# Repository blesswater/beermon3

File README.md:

beermon3

This is the thrid resurection of my beer refrigerator controller.

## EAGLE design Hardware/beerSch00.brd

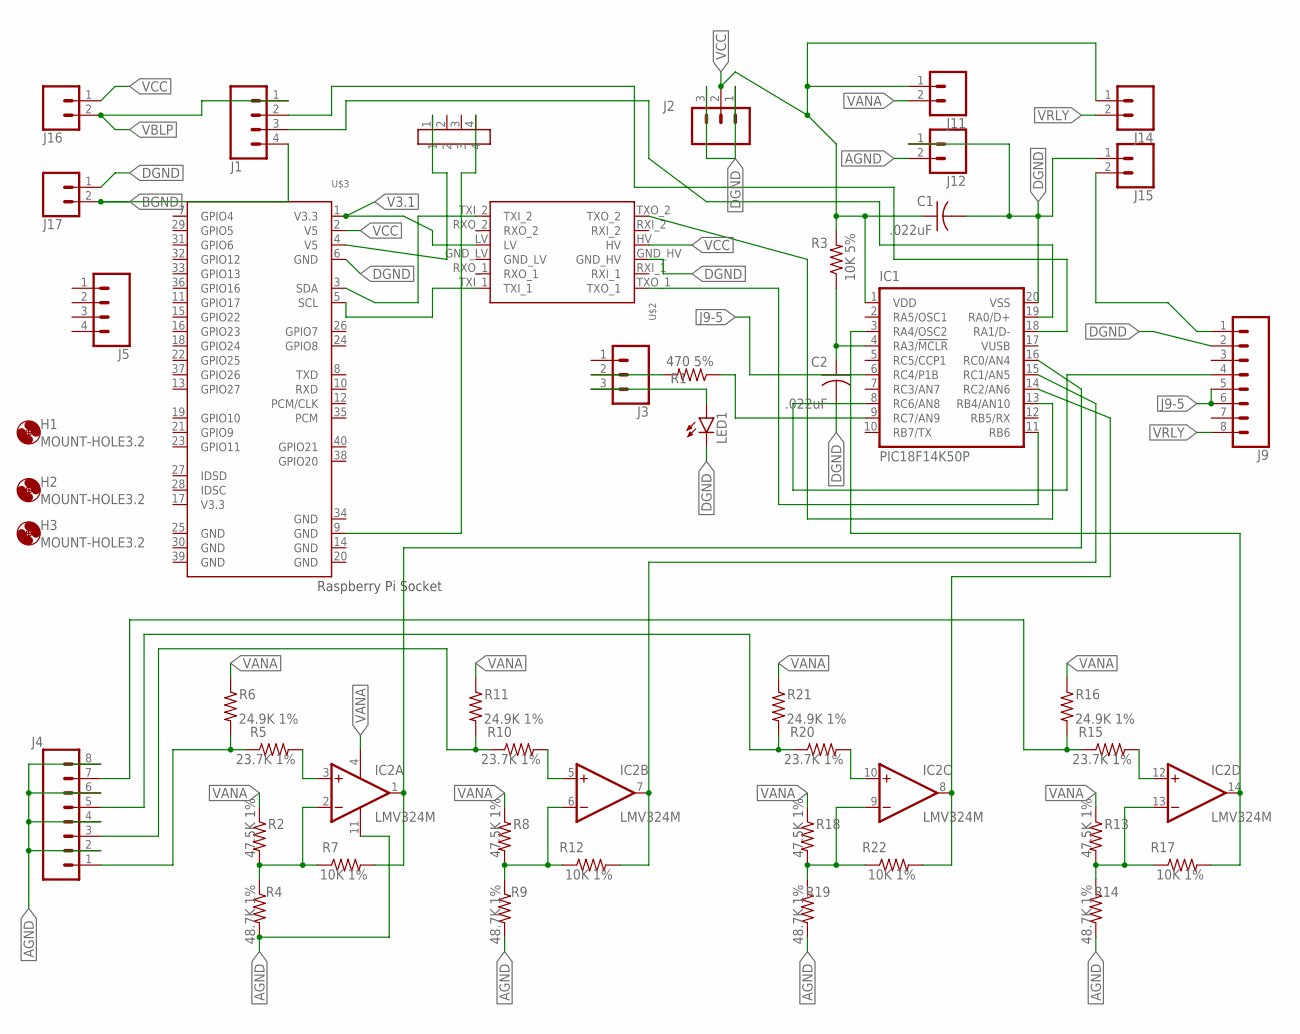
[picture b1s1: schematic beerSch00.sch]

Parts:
C1, C2: .022uF; C0805
H1, H2, H3: MOUNT-HOLE3.2; 3,2
IC1: PIC18F14K50P; DIL20
IC2: LMV324M; SO14
J1, J5: CONN_04; 1X04
J2, J3: CONN_03; 1X03
J4, J9: CONN_08"; 1X08
J11, J12, J14, J15, J16, J17: CONN_02; 1X02
LED1: LEDSML0805; SML0805
R1: 470 5%; R0603
R2, R8, R13, R18: 47.5K 1%; R0603
R3: 10K 5%; R0603
R4, R9, R14, R19: 48.7K 1%; R0603
R5, R10, R15, R20: 23.7K 1%; R0603
R6, R11, R16, R21: 24.9K 1%; R0603
R7, R12, R17, R22: 10K 1%; R0603
U$1: CONN_4; PINS_90
U$2: LEVELCONV; PLUG_THROUGHHOLE
U$3: RASPBERRYPI_SOCKET_UNDER; RASPBERRYPI_UNDERBD

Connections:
AGND: IC2.11 (V-), J4.2, J4.4, J4.6, J4.8, J12.2, R4.2, R9.2, R14.2, R19.2
BGND: J1.4, J17.2
DGND: C1.2, C2.2, IC1.20 (VSS), J2.1, J2.3, J9.2, J12.1, J15.1, J17.1, LED1.C, U$2.GND_HV, U$3.6 (GND)
J9-5: IC1.6 (RC4/P1B), J9.5, J9.6
unnamed: U$2.TXI_2, U$3.3 (SDA)
unnamed: U$2.TXI_1, U$3.5 (SCL)
unnamed: IC1.13 (RB4/AN10), U$2.TXO_2
unnamed: IC1.11 (RB6), U$2.TXO_1
unnamed: C2.1, IC1.4 (RA3/!MCLR!), R3.1
unnamed: J3.2, R1.2
unnamed: IC1.9 (RC7/AN9), R1.1
unnamed: J3.3, LED1.A
unnamed: IC2.2 (-IN), R2.2, R4.1, R7.1
unnamed: J4.1, R5.1, R6.2
unnamed: IC2.3 (+IN), R5.2
unnamed: IC1.16 (RC0/AN4), IC2.1 (OUT), R7.2
unnamed: IC2.6 (-IN), R8.2, R9.1, R12.1
unnamed: J4.3, R10.1, R11.2
unnamed: IC2.5 (+IN), R10.2
unnamed: J9.1, J15.2
unnamed: U$1.4, U$3.9 (GND)
unnamed: IC2.13 (-IN), R13.2, R14.1, R17.1
unnamed: J4.7, R15.1, R16.2
unnamed: IC2.12 (+IN), R15.2
unnamed: IC1.8 (RC6/AN8), J9.4
unnamed: IC2.9 (-IN), R18.2, R19.1, R22.1
unnamed: J4.5, R20.1, R21.2
unnamed: IC2.10 (+IN), R20.2
unnamed: U$1.1, U$3.4 (V5)
unnamed: IC1.19 (RA0/D+), J1.3
unnamed: IC1.3 (RA4/OSC2), IC2.14 (OUT), R17.2
unnamed: IC1.14 (RC2/AN6), IC2.8 (OUT), R22.2
unnamed: IC1.15 (RC1/AN5), IC2.7 (OUT), R12.2
unnamed: IC1.18 (RA1/D-), J1.2
V3.1: U$2.LV, U$3.1 (V3.3)
VANA: IC2.4 (V+), J11.2, R2.1, R6.1, R8.1, R11.1, R13.1, R16.1, R18.1, R21.1
VBLP: J1.1, J16.2
VCC: C1.1, IC1.1 (VDD), J2.2, J11.1, J14.1, J16.1, R3.2, U$2.HV, U$3.2 (V5)
VRLY: J9.8, J14.2

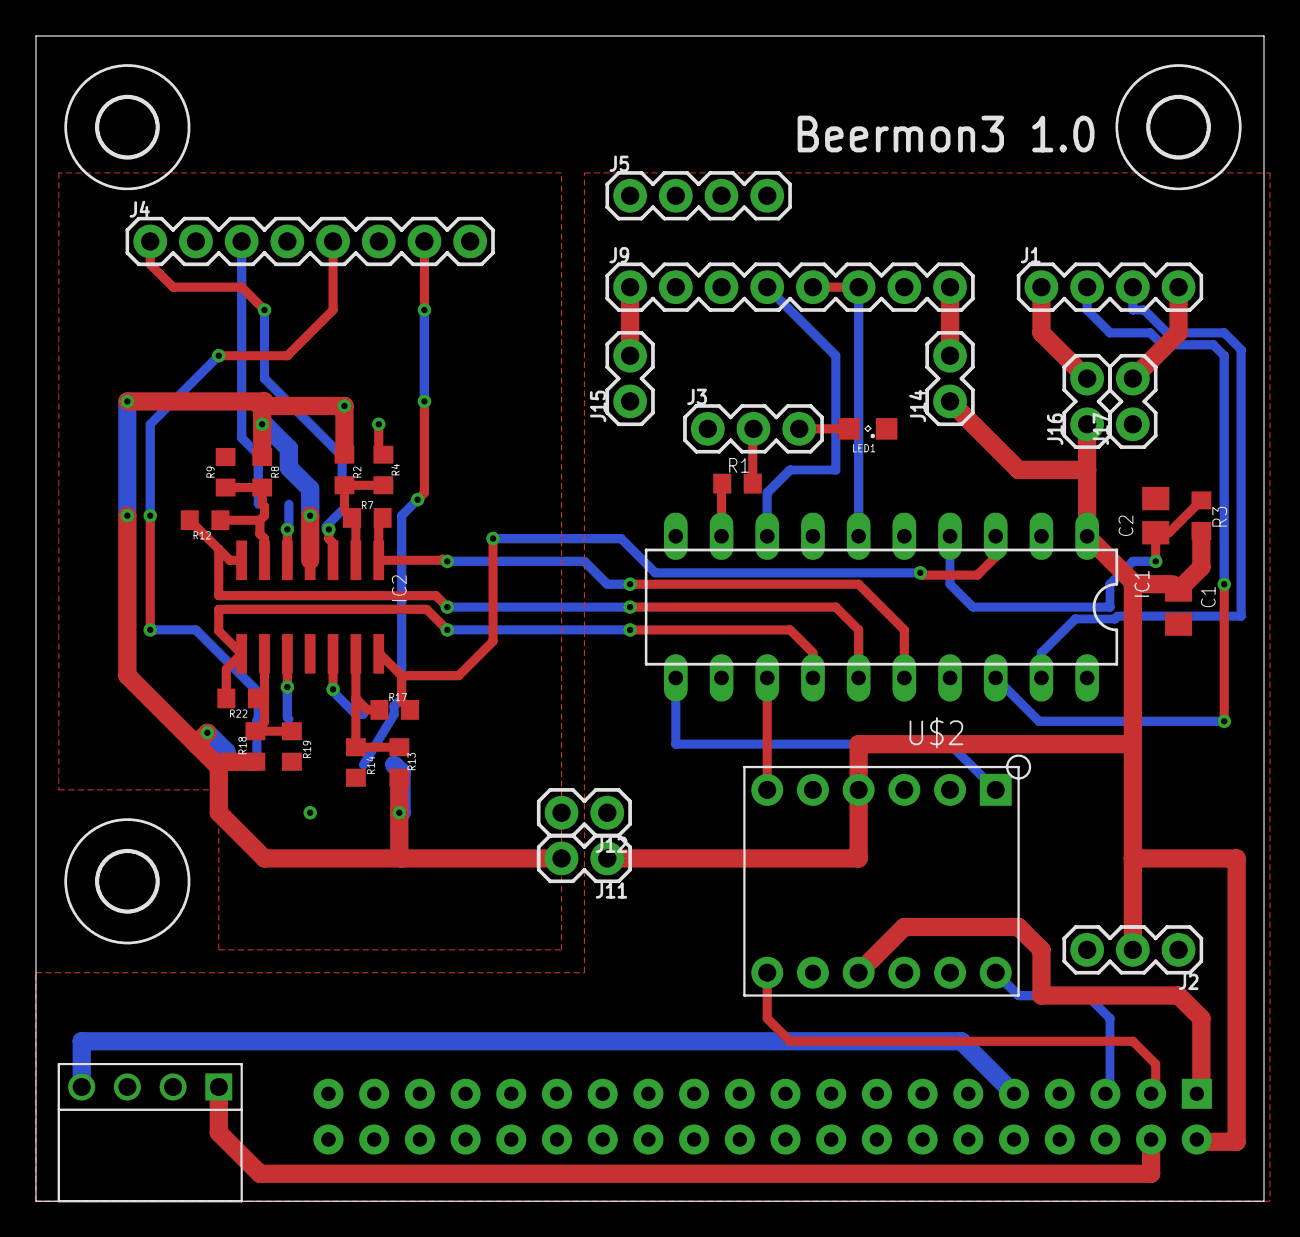
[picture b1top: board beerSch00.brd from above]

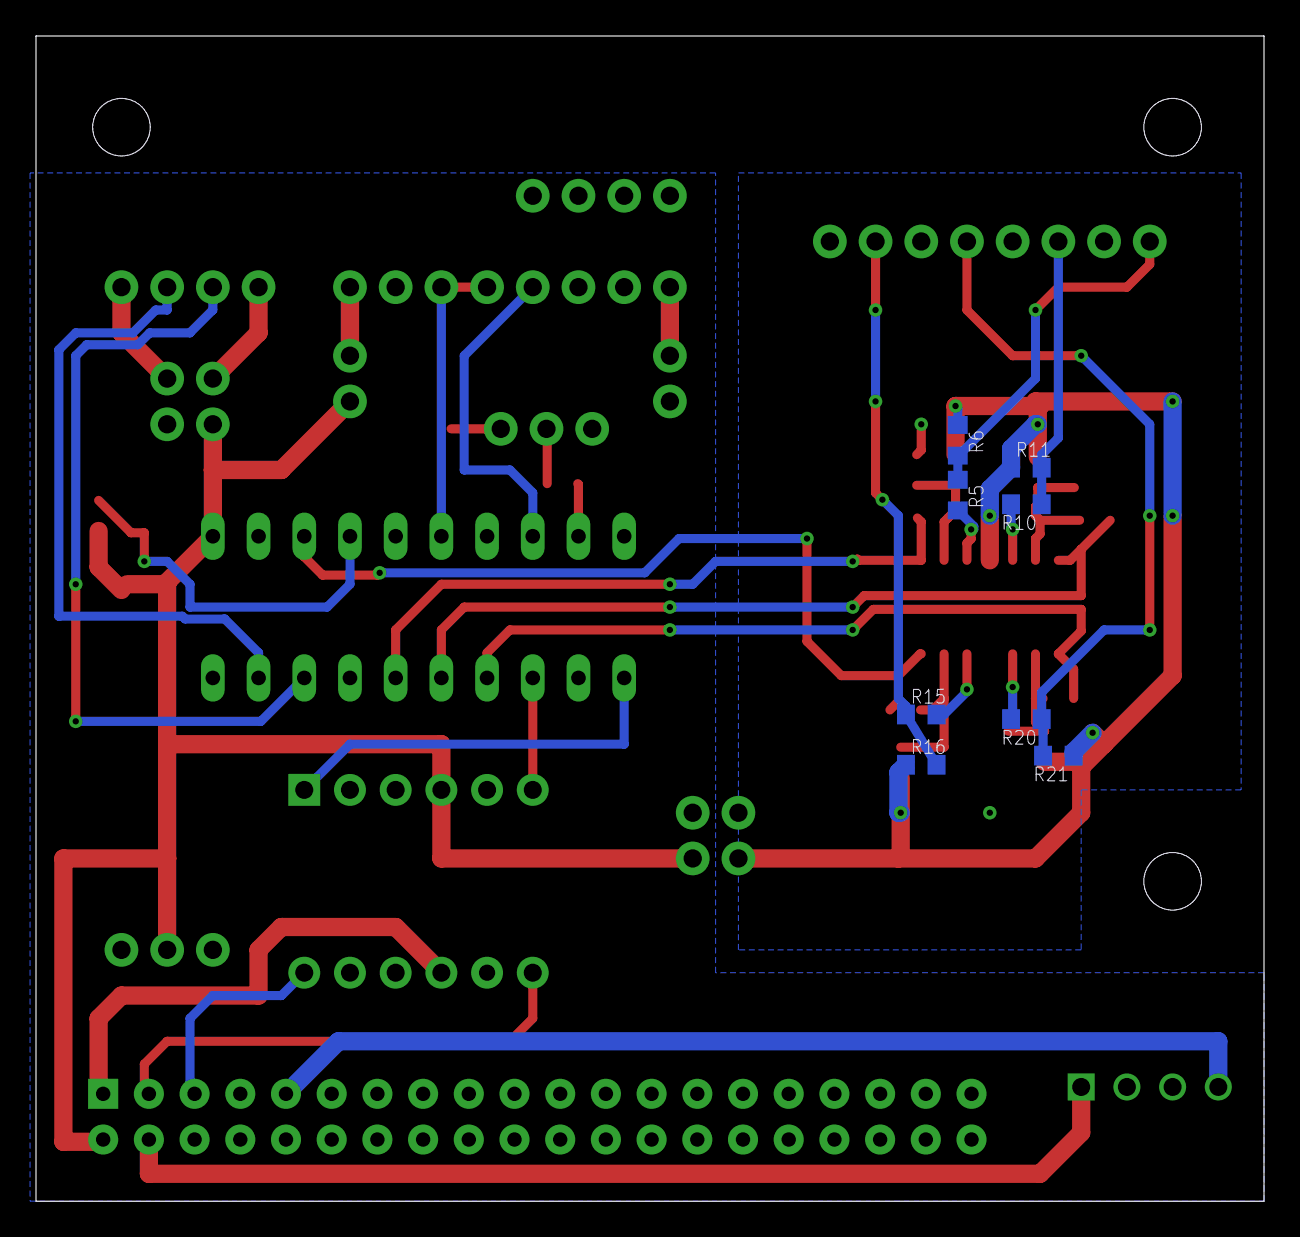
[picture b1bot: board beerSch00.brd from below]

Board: 2 copper layers, 68.2 x 64.8 mm, 45 parts (8 on the bottom side), 39 nets.

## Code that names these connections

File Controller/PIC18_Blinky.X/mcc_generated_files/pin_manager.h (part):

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// get/set channel_AN3 aliases
#define channel_AN3_TRIS                 TRISAbits.TRISA4
#define channel_AN3_LAT                  LATAbits.LATA4
#define channel_AN3_PORT                 PORTAbits.RA4
#define channel_AN3_WPU                  WPUAbits.WPUA4
#define channel_AN3_ANS                  ANSELbits.ANS3
#define channel_AN3_SetHigh()            do { LATAbits.LATA4 = 1; } while(0)
#define channel_AN3_SetLow()             do { LATAbits.LATA4 = 0; } while(0)
#define channel_AN3_Toggle()             do { LATAbits.LATA4 = ~LATAbits.LATA4; } while(0)
#define channel_AN3_GetValue()           PORTAbits.RA4
#define channel_AN3_SetDigitalInput()    do { TRISAbits.TRISA4 = 1; } while(0)
#define channel_AN3_SetDigitalOutput()   do { TRISAbits.TRISA4 = 0; } while(0)
#define channel_AN3_SetPullup()          do { WPUAbits.WPUA4 = 1; } while(0)
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// get/set SDA1 aliases
#define SDA1_TRIS                 TRISBbits.TRISB4
#define SDA1_LAT                  LATBbits.LATB4
#define SDA1_PORT                 PORTBbits.RB4
#define SDA1_WPU                  WPUBbits.WPUB4
#define SDA1_ANS                  ANSELHbits.ANS10
#define SDA1_SetHigh()            do { LATBbits.LATB4 = 1; } while(0)
#define SDA1_SetLow()             do { LATBbits.LATB4 = 0; } while(0)
#define SDA1_Toggle()             do { LATBbits.LATB4 = ~LATBbits.LATB4; } while(0)
#define SDA1_GetValue()           PORTBbits.RB4
#define SDA1_SetDigitalInput()    do { TRISBbits.TRISB4 = 1; } while(0)
#define SDA1_SetDigitalOutput()   do { TRISBbits.TRISB4 = 0; } while(0)
#define SDA1_SetPullup()          do { WPUBbits.WPUB4 = 1; } while(0)
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// get/set SCL1 aliases
#define SCL1_TRIS                 TRISBbits.TRISB6
#define SCL1_LAT                  LATBbits.LATB6
#define SCL1_PORT                 PORTBbits.RB6
#define SCL1_WPU                  WPUBbits.WPUB6
#define SCL1_SetHigh()            do { LATBbits.LATB6 = 1; } while(0)
#define SCL1_SetLow()             do { LATBbits.LATB6 = 0; } while(0)
#define SCL1_Toggle()             do { LATBbits.LATB6 = ~LATBbits.LATB6; } while(0)
#define SCL1_GetValue()           PORTBbits.RB6
#define SCL1_SetDigitalInput()    do { TRISBbits.TRISB6 = 1; } while(0)
#define SCL1_SetDigitalOutput()   do { TRISBbits.TRISB6 = 0; } while(0)
#define SCL1_SetPullup()          do { WPUBbits.WPUB6 = 1; } while(0)
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// get/set channel_AN4 aliases
#define channel_AN4_TRIS                 TRISCbits.TRISC0
#define channel_AN4_LAT                  LATCbits.LATC0
#define channel_AN4_PORT                 PORTCbits.RC0
#define channel_AN4_ANS                  ANSELbits.ANS4
#define channel_AN4_SetHigh()            do { LATCbits.LATC0 = 1; } while(0)
#define channel_AN4_SetLow()             do { LATCbits.LATC0 = 0; } while(0)
#define channel_AN4_Toggle()             do { LATCbits.LATC0 = ~LATCbits.LATC0; } while(0)
#define channel_AN4_GetValue()           PORTCbits.RC0
#define channel_AN4_SetDigitalInput()    do { TRISCbits.TRISC0 = 1; } while(0)
#define channel_AN4_SetDigitalOutput()   do { TRISCbits.TRISC0 = 0; } while(0)
#define channel_AN4_SetAnalogMode()      do { ANSELbits.ANS4 = 1; } while(0)
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// get/set channel_AN5 aliases
#define channel_AN5_TRIS                 TRISCbits.TRISC1
#define channel_AN5_LAT                  LATCbits.LATC1
#define channel_AN5_PORT                 PORTCbits.RC1
#define channel_AN5_ANS                  ANSELbits.ANS5
#define channel_AN5_SetHigh()            do { LATCbits.LATC1 = 1; } while(0)
#define channel_AN5_SetLow()             do { LATCbits.LATC1 = 0; } while(0)
#define channel_AN5_Toggle()             do { LATCbits.LATC1 = ~LATCbits.LATC1; } while(0)
#define channel_AN5_GetValue()           PORTCbits.RC1
#define channel_AN5_SetDigitalInput()    do { TRISCbits.TRISC1 = 1; } while(0)
#define channel_AN5_SetDigitalOutput()   do { TRISCbits.TRISC1 = 0; } while(0)
#define channel_AN5_SetAnalogMode()      do { ANSELbits.ANS5 = 1; } while(0)
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// get/set channel_AN6 aliases
#define channel_AN6_TRIS                 TRISCbits.TRISC2
#define channel_AN6_LAT                  LATCbits.LATC2
#define channel_AN6_PORT                 PORTCbits.RC2
#define channel_AN6_ANS                  ANSELbits.ANS6
#define channel_AN6_SetHigh()            do { LATCbits.LATC2 = 1; } while(0)
#define channel_AN6_SetLow()             do { LATCbits.LATC2 = 0; } while(0)
#define channel_AN6_Toggle()             do { LATCbits.LATC2 = ~LATCbits.LATC2; } while(0)
#define channel_AN6_GetValue()           PORTCbits.RC2
#define channel_AN6_SetDigitalInput()    do { TRISCbits.TRISC2 = 1; } while(0)
#define channel_AN6_SetDigitalOutput()   do { TRISCbits.TRISC2 = 0; } while(0)
#define channel_AN6_SetAnalogMode()      do { ANSELbits.ANS6 = 1; } while(0)
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// get/set IO_RC6 aliases
#define IO_RC6_TRIS                 TRISCbits.TRISC6
#define IO_RC6_LAT                  LATCbits.LATC6
#define IO_RC6_PORT                 PORTCbits.RC6
#define IO_RC6_ANS                  ANSELHbits.ANS8
#define IO_RC6_SetHigh()            do { LATCbits.LATC6 = 1; } while(0)
#define IO_RC6_SetLow()             do { LATCbits.LATC6 = 0; } while(0)
#define IO_RC6_Toggle()             do { LATCbits.LATC6 = ~LATCbits.LATC6; } while(0)
#define IO_RC6_GetValue()           PORTCbits.RC6
#define IO_RC6_SetDigitalInput()    do { TRISCbits.TRISC6 = 1; } while(0)
#define IO_RC6_SetDigitalOutput()   do { TRISCbits.TRISC6 = 0; } while(0)
#define IO_RC6_SetAnalogMode()      do { ANSELHbits.ANS8 = 1; } while(0)
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// get/set IO_RC7 aliases
#define IO_RC7_TRIS                 TRISCbits.TRISC7
#define IO_RC7_LAT                  LATCbits.LATC7
#define IO_RC7_PORT                 PORTCbits.RC7
#define IO_RC7_ANS                  ANSELHbits.ANS9
#define IO_RC7_SetHigh()            do { LATCbits.LATC7 = 1; } while(0)
#define IO_RC7_SetLow()             do { LATCbits.LATC7 = 0; } while(0)
#define IO_RC7_Toggle()             do { LATCbits.LATC7 = ~LATCbits.LATC7; } while(0)
#define IO_RC7_GetValue()           PORTCbits.RC7
#define IO_RC7_SetDigitalInput()    do { TRISCbits.TRISC7 = 1; } while(0)
#define IO_RC7_SetDigitalOutput()   do { TRISCbits.TRISC7 = 0; } while(0)
#define IO_RC7_SetAnalogMode()      do { ANSELHbits.ANS9 = 1; } while(0)
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
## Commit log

2018-03-24 Simple Blinky Running
2018-10-24 Add beerChip Project
2018-10-24 Remove lost files
2018-10-24 Change main
2018-10-24 Fixed arbituary file locations
2018-10-27 Added beerChip.ISR.c
2018-10-27 Got timer1 working
2018-10-30 Got I2C working
2018-10-30 Got LED control
2018-11-01 Got locks working
2018-11-02 Got MPLab v5.05 working
2018-11-02 Tested PIC3 on v5.05
2018-11-02 Commit stuff I do not want to commit to get merge to work
2018-11-02 Post-merge
2018-11-07 Add A2D files
2018-11-07 Worked on I2C A/D I/F
2018-11-07 Make build
2018-11-08 Got Chan 1 A/D working
2018-11-08 Version b
2018-11-09 Add thermister table
2018-11-11 Moved LED to RC7
2018-11-11 Added calculations
2018-11-21 Build beerChipTempLookup.c
2018-11-21 Before temp reading trigger
2018-11-21 Fixed bug in temp lookup
2018-11-22 Add user timer
2018-11-22 Added User timer to project
2018-11-22 Test commit
2018-11-22 Add relay board schematic
2018-11-24 Add relays and testing
2018-11-24 Build
2018-11-24 Test CI
2018-11-24 Remove relay test code
2018-11-26 Add beemon
2018-11-26 Add config to I2C
2018-11-27 Got beermon running
2018-11-27 More stuff
2018-11-28 Calc temp in A2D Reading
2018-11-29 Get beermon stats in
2018-12-01 Fix stopwatch
2018-12-01 Add start control
2018-12-01 Add i2c configuration
2018-12-05 Add SQLite database
2018-12-06 Add SQLite3 database
2018-12-08 Add logTemp
2018-12-08 Added Kiosk
2018-12-09 Add Kiosk and www
2018-12-09 Start uwsgi at startup
2018-12-11 Modify config
2018-12-12 Add RefMonitor directory
2018-12-12 Add Refmon files
2018-12-12 Add wwwGrab
2018-12-12 Add proj.sh and wwwPut.sh
2018-12-12 Add beerChipDB.py
2018-12-12 More stuff w/ wwwPut
2018-12-12 Add wwwConfig.sh
2018-12-14 Add configInfo.py
2018-12-15 Got headers processing working
2018-12-21 Get temperature stats
2018-12-25 Added and modifier thermometer.js
2018-12-25 Data timer
2018-12-28 therm stuff
2018-12-29 Add Session
2019-01-07 Add loginForm.html, RefMonitor/js/loginForm.js
2019-01-13 Add Probe select
2019-01-19 added Activets button
2019-01-19 Get rig of LEDs
2019-01-19 Version 4
2019-01-20 Fix kiosk session
2019-02-03 Add dial
2019-02-03 Add setSetpoint
2019-02-08 More work
2019-02-08 Ver 0.0.6
2019-02-09 Create html dir
2019-02-09 Started to migrate to the PIC18F14K50
2019-02-10 Add PIC18F_Blinky
2019-02-10 Add PIC_Beermon
2019-02-17 Get PIC18F14K50 beermon working
2019-02-18 Added all I2C functionality
2019-02-20 More PIC18F14K20
2019-02-20 Add beerChipBePersistant.py
2019-02-20 Notes
2019-02-20 Add beerChipPersistant.py
2019-02-21 Get persistance installed
2019-02-21 Fixed install.sh
2019-02-22 Fix Timers st startup
2019-02-22 Add stuff to installWeb.sh
2019-02-23 Added beerChipTempLookup.c
2019-02-26 Add probe 2
2019-03-02 Got 3 A/D Working
2019-03-02 Add beermon-persist.service and beermon-datacollect.service
2019-03-04 4th A/D channel
2019-03-04 Add 4 a/D chan
2019-05-11 Stuff
2019-05-11 Add Docs
2019-05-11 Add LMV324 Docs
2019-06-08 Add manual probes and cut sdev
2019-06-08 cut sdev
2019-06-29 Add makeBeerChipTempSpreadsheet.py
2019-06-29 MCLR Fix - late checkin
2019-06-29 Changed Low Voltage Program Config
2019-07-21 Add LED flash and bloopmon
2019-10-11 Start python BloopDet
2019-10-11 More bloop dector
2019-10-11 Add bloop det test
2019-10-11 Add bloop to logTemp.py
2019-10-11 Get right id
2019-10-11 Get right ts
2019-10-11 Get right
2019-10-11 Make event_time in ms
2019-10-20 Add beerChipBloopDet.c
2019-10-20 Add queryTemperature.py
2019-10-20 Put queryTemperature in the right place
2019-10-20 Try queryTemperature 00
2019-10-20 Fix usage
2019-10-20 stupid coma
2019-10-20 Working query Temp
2019-10-20 query Temperature
2019-10-21 Add notes
2019-10-21 Created Refrodge1 and paced logTemp.py
2019-10-31 Change Project
2019-11-03 Add testRelays
2019-11-11 Add schematic
2019-11-11 Add back panel
2019-11-29 Add setActiveProject and beermonStartup
2019-11-29 Add create Project
2019-11-30 Faster bloop detection
2019-11-30 Removed zeros in temperature query
2019-11-30 merge
2019-12-14 Improve install
2019-12-14 New initial DB
2019-12-14 Fix service and i2c group
2019-12-14 Fix kiosk install
2019-12-28 Get kiosh working
2019-12-28 Average reading
2019-12-28 Range check on temp reading
2020-01-07 Got test serial port working
2020-01-25 Serial Port - Hello World
2020-02-08 Serial Port
2020-02-08 installWeb.sh
2020-02-16 Add beerChipSerialLink.py beerChipRedis.py
2020-02-16 Serial port work
2020-02-16 Add beerChipSerialReader.py
2020-02-16 First beerChipRedis.py
2020-02-17 Get logtemp running
2020-02-17 Make Serrial Rx non-blocking
2020-02-17 Added serial Tx
2020-02-17 Tx Frame
2020-02-29 More Serial work
2020-02-29 Add more beerChipRedis
2020-02-29 Add relay test
2020-02-29 Get relay test working
2020-03-07 Start RedisReader at beer (service)
2020-03-14 Version
2020-03-15 Add Serial port bloop processing
2020-03-15 Add Beerchip serial bloop report
2020-03-15 Add Bloop processing
2020-03-15 Add bloop processing to beerChipRedis.py
2020-03-21 Fix Bloop Tx indication
2020-03-21 Add bloopdet Reset
2024-02-20 Pushing after a long time. Added gcode

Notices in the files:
Controller/PIC18_Blinky.X/mcc_generated_files/pin_manager.h:
(c) 2018 Microchip Technology Inc. and its subsidiaries.
parts and their libraries:
SparkFun-Connectors: Licensing: Creative Commons ShareAlike 4.0 International - https://creativecommons.org/licenses/by-sa/4.0
